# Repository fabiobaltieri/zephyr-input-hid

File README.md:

# Keyboard Matrix Testboard

A simple keyboard matrix board used for testing the Zephyr keyboard matrix
code.

## License (firmware)

This program is free software: you can redistribute it and/or modify
it under the terms of the GNU General Public License as published by
the Free Software Foundation, either version 3 of the License, or
(at your option) any later version.

## License (hardware)

Hardware files are licensed under a
Creative Commons Attribution-ShareAlike 4.0 International License.

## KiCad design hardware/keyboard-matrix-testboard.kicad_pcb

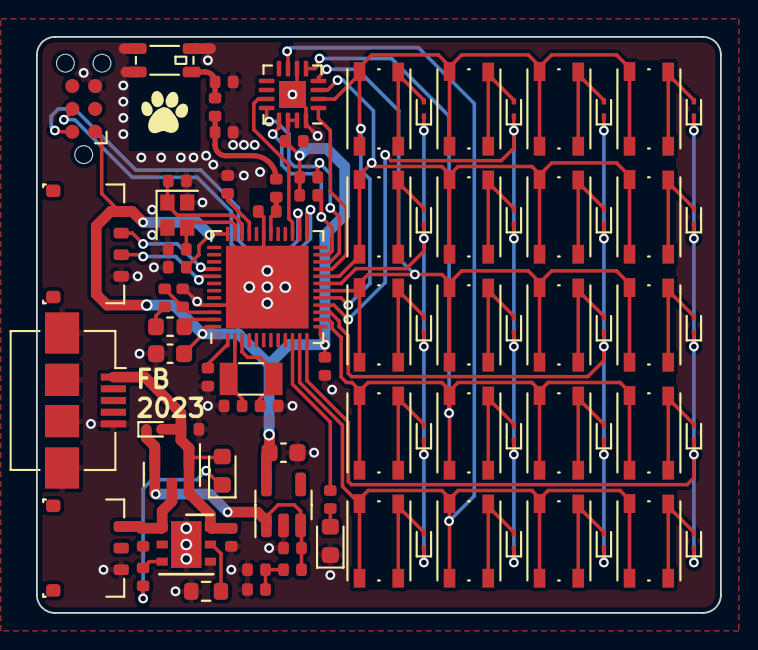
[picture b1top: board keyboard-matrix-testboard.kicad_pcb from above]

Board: 2 copper layers, 38.0 x 32.0 mm, 86 parts (0 on the bottom side), 60 nets.

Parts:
AE1: 2450AT18D0100001; 2450AT18D0100001-R
C1, C2, C3, C4: 12p; C_0402_Worthington
C5, C6, C15: 1u; C_0402_Worthington
C7, C9, C10, C11, C13, C14: 100n; C_0402_Worthington
C8: 100p; C_0402_Worthington
C12: 4.7u; C_0603_1608Metric
C16: 0.8p; C_0402_Worthington
C17, C19: TBD; C_0402_Worthington
C18: 10u; C_0603_1608Metric
D1, D2: Green; LED_0603_1608Metric
D3, D4, D5, D6, D7, D8, D9, D10, D11, D12, D13, D14, D15, D16, D17, D18, D19, D20, D21, D22, D23: 1SS416; D_SOD-923
J1: USB_B_Micro; USB_Micro-B_Amphenol_10104110_Horizontal
J2: EZmate-3
J3: EZmate-4
J5: TC2030-IDC-NL; Tag-Connect_TC2030-IDC-NL_2x03_P1.27mm_Vertical
L1: 15n; L_0402_Worthington
L2: 10u; L_0603_1608Metric
L3: 3.9n; L_0402_Worthington
L4: 0; L_0402_Worthington
Q1: BSS84; SOT-23
R1, R2: 560k; R_0402_Worthington
R3: 2k2; R_0603_1608Metric
R4, R5: 1k; R_0402_Worthington
R6, R7: 4.7k; R_0402_Worthington
R8: 10k; R_0402_Worthington
SW1, SW2, SW3, SW4, SW5, SW6, SW7, SW8, SW9, SW10, SW11, SW12, SW13, SW14, SW15, SW16, SW17, SW18, SW19, SW20: SW_Push; SW_Push_1P1T_NO_Vertical_Wuerth_434133025816
U1: STBC08; DFN-6-1EP_3x3mm_P0.95mm_EP1.7x2.6mm
U2: nRF52832-QFxx; QFN-48-1EP_6x6mm_P0.4mm_EP4.6x4.6mm
U3: MIC5301; SOT-23-5
U4: PCAL6408A; HVQFN-16-1EP_3x3mm_P0.5mm_EP1.5x1.5mm
Y1: 32.768kHz; Crystal_SMD_3215-2Pin_3.2x1.5mm
Y2: 32MHz; Crystal_SMD_2016-4Pin_2.0x1.6mm

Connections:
+3V3: C9.1, C11.1, C12.1, C14.1, C18.1, J3.1, J5.1, R6.1, R7.1, U2.13 (VDD), U2.36 (VDD), U2.48 (VDD), U3.5 (OUT), U4.14 (VDD(P)), U4.15 (VDD(I2C-bus))
+5V: C6.1, D2.2 (A), D3.2 (A), J1.1 (VBUS), Q1.1 (G), R8.1, U1.6 (VCC)
+BATT: C13.1, J2.1, Q1.3 (D), U1.1 (BAT)
/ADC_VBATT: C7.1, R1.2, R2.1
/ANT: C16.1, L3.2, U2.30 (ANT)
/CHRG: R5.2, U1.3 (CHRG)
/COL0: D4.1 (K), D5.1 (K), D6.1 (K), D7.1 (K), D8.1 (K), U2.19 (P0.16)
/COL1: D9.1 (K), D10.1 (K), D11.1 (K), D12.1 (K), D13.1 (K), U2.16 (P0.13)
/COL2: D14.1 (K), D15.1 (K), D16.1 (K), D17.1 (K), D18.1 (K), U2.15 (P0.12)
/COL3: D19.1 (K), D20.1 (K), D21.1 (K), D22.1 (K), D23.1 (K), U2.12 (NFC2/P0.10)
/IOEXP_INT: U2.27 (P0.22), U4.11 (INT)
/IOEXP_RESET: U2.21 (P0.18/SWO), U4.1 (RESET)
/LED_A: R4.1, U2.10 (P0.08)
/NRF_SWCLK: J5.4, U2.25 (SWDCLK)
/NRF_SWDIO: J5.2, U2.26 (SWDIO)
/ROW0: SW1.1, SW6.1, SW11.1, SW16.1, U2.17 (P0.14), U4.2 (P0)
/ROW1: SW2.1, SW7.1, SW12.1, SW17.1, U2.20 (P0.17), U4.3 (P1)
/ROW2: SW3.1, SW8.1, SW13.1, SW18.1, U2.18 (P0.15), U4.4 (P2)
/ROW3: SW4.1, SW9.1, SW14.1, SW19.1, U2.14 (P0.11), U4.5 (P3)
/ROW4: SW5.1, SW10.1, SW15.1, SW20.1, U2.11 (NFC1/P0.09), U4.7 (P4)
/SCL: R7.2, U2.22 (P0.19), U4.12 (SCL)
/SDA: R6.2, U2.23 (P0.20), U4.13 (SDA)
/UART_RX: J3.2, U2.40 (P0.28/AIN4)
/UART_TX: J3.3, U2.41 (P0.29/AIN5)
/XL1: C2.1, U2.2 (P0.00/XL1), Y1.2
/XL2: C4.1, U2.3 (P0.01/XL2), Y1.1
GND: AE1.2 (Shield), C1.2, C2.2, C3.2, C4.2, C5.2, C6.2, C7.2, C8.2, C9.2, C10.2, C11.2, C12.2, C13.2, C14.2, C15.2, C16.2, C17.2, C18.2, C19.2, D1.1 (K), J1.5 (GND), J1.6 (Shield), J2.3, J3.4, J5.5, R2.2, R3.2, R8.2, U1.4 (GND), U1.7 (TH), U2.31 (VSS), U2.45 (VSS), U2.49 (VSS), U3.2 (GND), U4.6 (VSS), U4.16 (ADDR), U4.17 (TH), Y2.2, Y2.4
unnamed: AE1.1 (A), C19.1, L4.1
unnamed: C17.1, L3.1, L4.2
unnamed: D1.2 (A), R4.2
unnamed: D2.1 (K), R5.1
unnamed: D4.2 (A), SW1.2
unnamed: D5.2 (A), SW2.2
unnamed: D6.2 (A), SW3.2
unnamed: D7.2 (A), SW4.2
unnamed: D8.2 (A), SW5.2
unnamed: D9.2 (A), SW6.2
unnamed: D10.2 (A), SW7.2
unnamed: D11.2 (A), SW8.2
unnamed: D12.2 (A), SW9.2
unnamed: D13.2 (A), SW10.2
unnamed: D14.2 (A), SW11.2
unnamed: D15.2 (A), SW12.2
unnamed: D16.2 (A), SW13.2
unnamed: D17.2 (A), SW14.2
unnamed: D18.2 (A), SW15.2
unnamed: D19.2 (A), SW16.2
unnamed: D20.2 (A), SW17.2
unnamed: D21.2 (A), SW18.2
unnamed: D22.2 (A), SW19.2
unnamed: D23.2 (A), SW20.2
unnamed: L1.2, L2.2
unnamed: R3.1, U1.5 (PROG)
unnamed: L2.1, U2.47 (DCC)
unnamed: C10.1, U2.1 (DEC1)
unnamed: C8.1, U2.33 (DEC3)
unnamed: C5.1, L1.1, U2.46 (DEC4)
unnamed: C1.1, U2.34 (XC1), Y2.1
unnamed: C3.1, U2.35 (XC2), Y2.3
VCC: C15.1, D3.1 (K), Q1.2 (S), R1.1, U3.1 (IN), U3.3 (EN)

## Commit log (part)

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2023-11-24 hw: assembly tweaks
2023-11-24 firmware: initial import
2023-11-27 fw: change dts placeholderes
2023-11-29 fw: add main blinky
2023-11-29 fw: add few more commented props
2023-12-07 fw: update CONFIG_INPUT_SHELL_KBD_MATRIX_STATE
2023-12-14 zephyr-doc-figures: added figures for the Zephyr documentation
2023-12-15 fw: drop bas from adv
2023-12-17 hw: add a note about the missing adc_vbatt connection
2023-12-17 fw: drop the batt stuff, forgot to connect it :-(
2023-12-18 zephyr-doc-figures: update style and refdes
2024-01-19 fw: disable ghost check, remap keys
2024-01-19 fw: enable flash, settings, bt smp
2024-01-19 fw: add ble_hog
2024-01-19 add README
2024-01-20 fw: use the input-hid functions
2024-01-23 build: add a manifest and build workflow
2024-01-26 fw: map few extra keys
2024-02-11 fw: add softreset to nrfjprog runner option
2024-02-14 fw: drop stray blank line
2024-02-28 fw: enable port expander and drive inactive by default
2024-02-28 hw: fix note format
2024-03-31 fw: refactor kbd hid data out
2024-03-31 fw: use the report size define in the desriptor
2024-04-02 fw: use 8 bit min/max
2024-04-02 fw: add nkro support
2024-04-05 fw: add locking
2024-04-11 fw: use an intermediate variable for the kbd attr
2024-04-18 fw: refactor the hid report code and structures
2024-04-20 fw: add an nrf52dk overlay
2024-04-20 build: build for nrf52dk
2024-04-20 fw: add a Kconfig for NKRO protocol
2024-04-21 fw: split bt config out
2024-04-21 fw: add usb hid support
2024-04-21 fw: add darfon support
2024-04-21 fw: move keypad data together
2024-04-21 fw: blank line
2024-04-21 fw: add hal_stm32
2024-04-21 fw: add few notes on the darfon keys
2024-04-21 fw: add usb nkro support
2024-04-22 build: add firmware artifacts
2024-04-22 build: update checkout to v4
2024-04-23 fw: darfon: add cdc-acm definition, off by default
2024-04-23 fw: switch to BT_LE_ADV_CONN
2024-04-24 fw: swap mutex with sem
2024-04-24 fw: drop few labels
2024-04-24 fw: add a config for nrf52dk
2024-04-29 fw: move darfon.c under boards
2024-04-29 fw: change bt device name
2024-04-29 fw: clean main.c
2024-05-12 fw: rename the blinker callback
2024-05-12 fw: tweak few options
2024-05-12 fw: move bt config in Kconfig
2024-05-12 fw: move usb options in kconfig
2024-05-17 fw: drop stale struct from ble_hog.h
2024-05-18 fw: drop .h files from cmakelists
2024-05-18 fw: move the reports in devicetree
2024-05-18 fw: rename ble_report_map
2024-05-18 fw: add an hid device
2024-05-18 fw: port over the mouse callback code
2024-05-18 fw: drop a cuple comments
2024-05-18 fw: create ble stuff from dt
2024-05-18 fw: drop HID_REPORT_ID_KBD
2024-05-18 fw: add hog support for multiple hog services
2024-05-19 fw: hid stack
2024-05-19 fw: drop more comments
2024-05-19 fw: fix output report def
2024-05-20 fw: log style fixes
2024-05-20 fw: split up the usb device struct flash/ram
2024-05-20 fw: spaces/tab
2024-05-20 fw: notify asyncronously
2024-05-20 fw: add an input subnode
2024-05-20 fw: add an output subnode
2024-05-21 fw: restructure usb_hid
2024-05-21 fw: fix up cmakelist
2024-05-21 fw: restructure ble_hog
2024-05-21 fw: missing const qualifier
2024-05-21 fw: add a hog notify device mask
2024-05-21 fw: hid auto cache size
2024-05-23 fw: implement no change detection
2024-05-23 fw: set mouse buttons on nrf52dk
2024-05-23 fw: fix hids report format
2024-05-23 fw: finish fixing the report thing
2024-05-23 fw: add mouse support
2024-05-23 fw: setup nrf52dk for mouse testing
2024-05-23 fw: drop the hid wrappers
2024-05-23 fw: dts rename
2024-05-23 fw: add a gamepad driver
2024-05-23 fw: tweak nrf52dk more
2024-05-24 fw: fix wrong \ indentation
2024-05-25 fw: add kbd leds support and usb/hog write stubs
2024-05-25 fw: change dongle button code
2024-05-25 fw: drop the hid_has_updates api
2024-05-25 fw: hid style changes
2024-05-25 fw: tweak few kconfig
2024-05-25 fw: add output report support to hid and kbd
2024-05-25 build: add nrf52840dongle
2024-05-26 fw: add a report copy path
2024-05-26 fw: fix usb write out dev type
2024-05-28 fw: fix ble return code
2024-06-04 fw: switch to the new usb api
2024-06-04 fw: clean up usbd.c, add mfg and device name options
2024-06-04 fw: move few defaults to kconfig
2024-06-04 fw: drop the suspend code, needs to be redone anyway
2024-06-04 fw: usbd refactor
2024-06-06 fw: adjust few polling rate definitions
2024-06-14 fw: usb property update
2024-06-26 fw: add pmw-testboard support
2024-06-26 fw: build for pmw_testboard
2024-06-26 fw: add flash-dongle.sh script
2024-06-26 fw: add paw-testboard
2024-06-26 build: add paw-testboard
2024-06-26 fw: fix wrong sw_c identifiers
2024-06-27 fw: add multiple input dev support to gamepad and hid
2024-07-03 fw: add analog-axis-shell.c
2024-07-03 fw: add zalpakka
2024-07-03 build: add zalpakka
2024-07-04 fw: add drv8212 binding
2024-07-05 fw: blink on bt unpair shell, set led on nrf52dk
2024-07-05 fw: configure unpair from devicetree
2024-07-05 fw: rename system to led_blinker
2024-07-05 fw: rework zalpakka switch config
2024-07-05 fw: add led poweroff, rename blinker defines
2024-07-05 fw: add ble stop
2024-07-05 fw: add auto poweroff
2024-07-06 fw: add regulator shutdown support
2024-07-06 fw: switch few options to configdefault
2024-07-06 fw: add suspend gpio support
2024-07-07 fw: implement device enable/disable
2024-07-08 fw: set unpair combo for kbd_matrix
2024-07-08 fw: set sense-edge-mask for kbd_matrix
2024-07-09 fw: label kbd-matrix so it gets pm events
2024-07-09 fw: add missing suspend-gpios binding
2024-07-10 fw: add few missing defines
2024-07-10 fw: rename darfon.c to clicker.c
2024-07-10 fw: add led cb support
2024-07-10 fw: darfon: add caps led support
2024-07-15 fw: set device appearance automatically
2024-07-15 fw: enable reboot command
2024-07-15 fw: split out usbd.c build entry
2024-07-15 fw: drop USBD_HID_SUPPORT override
2024-07-17 fw: add negcon-retro board
2024-07-18 fw: add ble-pulse-encoder
2024-07-18 fw: add few modules
2024-07-18 build: add ble-pulse-encoder
2024-07-18 add ble_pulse_encoder/flash_mcuboot
2024-07-19 fw: reduce the adc bas threshold a bit
2024-07-19 fw: call usbd_device_set_code_triple directly
2024-07-20 fw: make usb vid/pid/power configurable
2024-07-21 fw: implement hog/usbhid power management hooks
2024-07-21 fw: rework the analog axis calibration command
2024-07-21 fw: fix zalpakka hat pins
2024-07-21 fw: add initial xinput support
2024-07-22 fw: rename led_blinker to led_status
2024-07-24 fw: add ds2-retrofit
2024-07-24 fw: add bas_fuel_gauge
2024-07-24 fw: add drv8830
2024-07-26 fw: fix ds2-retrofit unpair codes
2024-07-26 fw: add few debounce-interval-ms props
2024-07-26 fw: blink less
2024-07-26 fw: add xinput hs support
2024-07-26 fw: rename few dt nodes
2024-07-26 fw: add remote wakeup config
2024-07-26 fw: add xinput out support
2024-07-26 fw: drop paw from nrf52dk
2024-07-26 fw: replace blinker with an event queue
2024-07-26 fw: add hal_nxp
2024-07-27 fw: update axis inversion properties
2024-07-27 fw: clean few log messages
2024-07-28 fw: add usb status detection-ish
2024-07-28 fw: add panic.c
2024-07-28 fw: silence blinker queue full message
2024-07-28 fw: use reboot define
2024-07-28 fw: drop CONFIG_LOG_BACKEND_UART=y for nrf52dk
2024-07-29 fW: turn few more shell commands off by default
2024-07-29 fw: clean cc changed log message
2024-07-29 fw: add missing include
2024-07-29 fw: drop id from ble status
2024-07-29 fw: request L2 security on ble connect
2024-07-29 fw: add hog shell for target selection
2024-07-29 fw: add ble status command
2024-07-29 fw: move bt shell on its own file
2024-07-31 fw: input api update
2024-07-31 fw: header cleanup
2024-08-01 fw: add paw_pogo
2024-08-09 fw: error out on charger NULL
2024-08-09 fw: indentation fix
2024-08-09 fw: flip buttons
2024-08-09 fw: add gpio charger status support
2024-08-11 fW: change poweroff disconnect code
2024-08-11 fw: add a ble disconnect command
2024-08-12 fw: fix leaking conn ref
2024-08-17 fw: add hires wheel descriptor
2024-08-17 fw: add set feature support
2024-08-17 fw: rename hid_out_report
2024-08-17 fw: fix wrong set feature check condition
2024-08-17 fw: add mouse feat support
2024-08-17 fw: add pat hi res wheel support
2024-08-17 fw: pogo: swap the scroller axis
2024-08-17 fw: rework hid_mouse and hid_kbd cb handle code
2024-08-24 fw: set max paired to 2 for ds2 retro
2024-08-24 fw: do not power off while charging
2024-08-29 fw: drop unused include
2024-08-30 fw: rename fuel_gauge to fuel_gauge_sensor
2024-08-30 fw: rework the subsys fuel gauge code
2024-09-07 fw: drop few stray blank lines
2024-09-20 fw: update mcumgr options
2024-09-24 fw: add paw_g3
2024-09-25 fw: move LOG_PROCESS_THREAD_SLEEP_MS default to Kconfig
2024-09-25 fw: add a binding for board specific input event filters
2024-09-25 build: chew up the board name for finding the key
2024-09-25 build: upload signed files
2024-09-26 fw: remap ploopy mouse keys
2024-09-26 fw: add few flash scripts
2024-09-26 fw: repartition paw_g3
2024-09-28 fw: enable MCUMGR_GRP_IMG_ALLOW_ERASE_PENDING by default
2024-09-30 fw: set CONFIG_ROM_END_OFFSET and CONFIG_MCUBOOT_UPDATE_FOOTER_SIZE
2024-09-30 fw: fix usb report size limit
2024-09-30 fw: implement get report
2024-09-30 build: clean up gh env
2024-10-01 hw: drop keyboard-matrix-testboard
2024-10-01 fw: implement hog read_input_report
2024-10-04 fw: g3: fix the scroller setup
2024-10-04 fw: move event.h in include/
2024-10-05 fw: add fuel gauge error handling
2024-10-07 g3: enable pat sleep states
2024-10-07 fw: hid_kbd ignore non key events
2024-10-08 fw: update ble options
2024-10-09 fw: setup mcuboot for paw_g3
2024-10-09 fw: add activity blink timeout support
2024-10-13 fw: switch to pm runtime, add pm control, i2c changes etc
2024-10-19 fw: drop the twim/spi overrides, just use the default
2024-11-16 fw: use led_dt_spec
2024-11-17 fw: one more led_dt_spec
2024-11-27 fw: add rtt to kbd-matrix
2024-11-27 fw: use the new device apis
2024-11-27 fw: add a filter to the hid command device list
2024-11-27 fw: add a filter to hog_peer as well
2024-11-28 fw: disable bluetooth assertions by default
2024-11-28 fw: drop tinycrypt
2024-12-15 fw: set usb config names
2024-12-19 fw: add empty ad when bonded support
2024-12-20 fw: save ploopy mouse addr
2024-12-20 fw: enable empty add on few devices
2024-12-29 fw: add directed adv support
2025-01-10 fw: syntax fix
2025-01-10 fw: enable directed adv only if max_paired == 1
2025-01-15 fw: usb hid api update
2025-01-28 fw: add support for peer disconnect when fully bonded
2025-02-04 fw: drop DEVICE_DT_GET_BY_IDX
2025-02-04 fw: usb api update
2025-02-04 fw: fix potential deadlock
2025-02-04 fw: flip few disconnect when bonded options
2025-02-05 fw: drop --softreset from all boards, this is now default
2025-05-03 fw: allow empty connect-on
2025-05-03 fw: add big_stick board
2025-05-17 fw: add g3 nus console, tweak few configs
2025-05-17 fw: fix big stick unpair combo
2025-05-23 fw: big_stick add pyocd
2025-07-27 fw: kbd matrix default to nrfjprog
2025-07-27 fw: kbd matrix drop the rx pullup
2025-07-27 fw: paw g3 fix partition addr
2025-08-01 fw: fuel gauge api update
2025-08-03 fw: add watchdog on sysworkq
2025-08-03 fw: add few missing static
2025-09-08 build: set a ccache cache key
2025-11-05 build: add wasd_kbd
2025-11-07 fw: missing static
2025-11-07 fw: wasd: default to dfu-util
2025-11-07 fw: wasd-kbd: setup dma on the led strip
2025-11-07 fw: wasd: change cycles to 40
2025-11-07 wasd: drop redundant return
2025-11-08 fw: fix project name
2025-11-08 fw: wasd_kbd: use 1ms polling
2025-11-08 fw: add hid suspend events
2025-11-08 fw: wasd-kbd: add bootloader support
2025-11-08 fw: wasd: tab fix
2025-12-25 fw: disable wdt on darfon
2025-12-25 fw: use DT_FREQ_M
2026-01-07 fw: set board full_name
2026-02-03 fw: add long press reboot
2026-03-14 g3: enable bt dis
2026-03-14 fw: g3: back to rtt console
2026-03-14 hid: implement hi res wheel debouncing
2026-03-20 fw: tweak the wheel debouncing threshold up
2026-03-21 west: add tf-psa-crypto
2026-03-21 fw: fix few llvm warnings
2026-03-21 fw: convert constant to double
2026-03-24 fw: fix llvm warning
2026-03-24 fw: min/max/clamp
2026-04-29 fw: use zephyr,mapped-partition
2026-05-14 boards: input api update
2026-05-20 fw: add missing minmax.h
2026-06-13 fw: fuel gauge: update defines
